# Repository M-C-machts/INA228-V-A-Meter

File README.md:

# INA228-V-A-Meter

A KiCad 9 hardware project for a compact voltage and current meter/logger using:
- **TI INA228** - high-accuracy current/voltage/power monitor
- **Seeed XIAO ESP32-C3** - MCU module

The board is **powered from a LiFePO₄ battery** and charged via the **XIAO's USB-C port**.

> **Status:** Work in progress. Some changes may occur.

---

## Features
- Simultaneous **bus voltage** and **current** measurement via INA228
- ESP32-C3 firmware
- LiFePO₄ battery powered - portable
- 1.3" OLED display

---

## Hardware Overview
### Main Components
- **INA228**: measures shunt and bus voltage; performs current/power calculations internally
- **XIAO ESP32-C3**: reads INA228 over **I²C** and outputs/logs data
- LiFePO₄ charge/discharge power management is handled via a daughter board: [XIAO-LiFePO4-Power-Module](https://github.com/M-C-machts/XIAO-LiFePO4-Power-Module)
- Gerber files for PCB fabrication are included
- Case files for 3D printing are included

### Power
- The board is powered by a **LiFePO₄ cell**.
- Charging is handled **through the XIAO USB-C port** via the daughter board. The XIAO's onboard charger/power path is not used.
- To use a LiPo battery instead, omit the XIAO-LiFePO4-Power-Module and connect a *protected* LiPo battery directly to the XIAO battery solder pads.

---

## Firmware
- Reads INA228 registers via I²C
- Calculates and displays:
  - Voltage (V)
  - Current (A)
  - Power (W) *(optional)*
- Outputs data over USB serial and 1.3" OLED display

## Calibration / Accuracy Notes
INA228 measurement accuracy depends heavily on:
- Shunt resistor value, tolerance, and temperature coefficient
- Correct INA228 configuration (averaging, conversion times, calibration register)

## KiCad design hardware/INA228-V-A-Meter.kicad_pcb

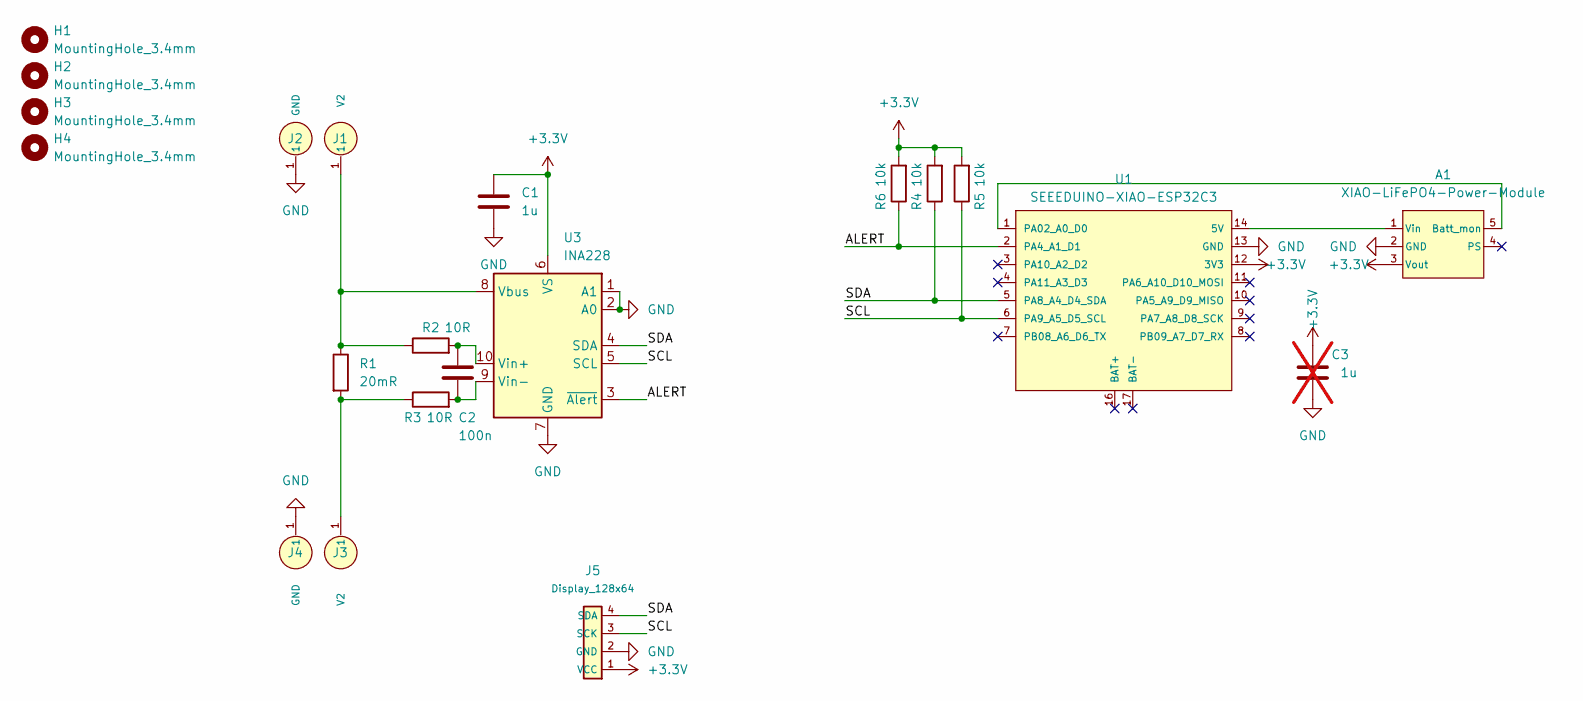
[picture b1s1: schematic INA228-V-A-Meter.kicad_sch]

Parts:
A1: XIAO-LiFePO4-Power-Module
C1: 1u; C_0603_1608Metric
C2: 100n; C_0603_1608Metric
C3: 1u; C_0805_2012Metric; not fitted
H1, H2, H3, H4: MountingHole_3.4mm; MountingHole_3.2mm_M3
J1, J2, J3, J4: Banana-Socket; banana-socket; Mouser Part Number 534-575-4
J5: Display-OLED-1.3-Module
R1: 20mR; R_2512_6332Metric
R2, R3: 10R; R_0805_2012Metric
R4, R5, R6: 10k; R_0805_2012Metric
U1: SEEEDUINO-XIAO-ESP32C3
U3: INA228; VSSOP-10_3x3mm_P0.5mm

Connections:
+3.3V: A1.3 (Vout), C1.1, C3.1, J5.1 (VCC), R4.2, R5.2, R6.2, U1.12 (3V3), U3.6 (VS)
/ALERT: R6.1, U1.2 (PA4_A1_D1), U3.3 (~Alert)
/SCL: J5.3 (SCK), R5.1, U1.6 (PA9_A5_D5_SCL), U3.5 (SCL)
/SDA: J5.4 (SDA), R4.1, U1.5 (PA8_A4_D4_SDA), U3.4 (SDA)
GND: A1.2 (GND), C1.2, C3.2, J2.1, J4.1, J5.2 (GND), U1.13 (GND), U3.1 (A1), U3.2 (A0), U3.7 (GND)
unnamed: A1.5 (Batt_mon), U1.1 (PA02_A0_D0)
unnamed: A1.1 (Vin), U1.14 (5V)
unnamed: J3.1, R1.2, R3.1
unnamed: J1.1, R1.1, R2.1, U3.8 (Vbus)
unnamed: C2.1, R2.2, U3.10 (Vin+)
unnamed: C2.2, R3.2, U3.9 (Vin-)

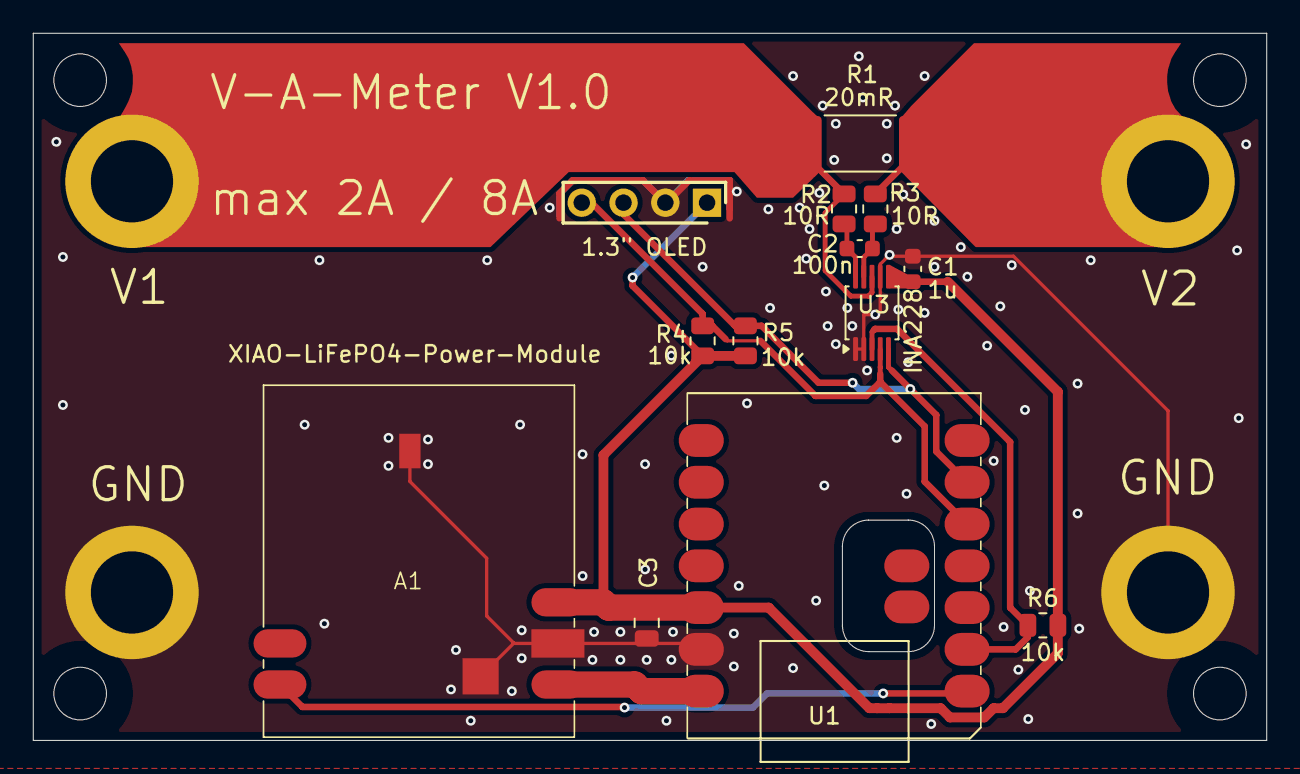
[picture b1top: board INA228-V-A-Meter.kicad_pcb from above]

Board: 2 copper layers, 75.0 x 43.0 mm, 21 parts (0 on the bottom side), 11 nets.

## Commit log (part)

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2026-02-19 Add V-A-Meter Project, needs testing
2026-02-21 Rename
2026-04-06 Rework PCB
2026-04-06 Save
2026-04-06 Rework PCB, Add fabrication and case
2026-04-06 Small rewrite
